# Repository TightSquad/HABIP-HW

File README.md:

# The Custom PCB Hardware repo for the HABIP
Main code repo for the HABIP: [HABIP](https://github.com/TightSquad/HABIP "HABIP Repo")

MSP430 firmware repo for the HABIP: [HABIP-MSP430](https://github.com/TightSquad/HABIP-MSP430 "HABIP-MSP430 Repo")

Communication Systems Team Website: [COMMS](http://edge.rit.edu/edge/P17104/public/Home "COMM's Website")

Data Acquisition & Control Systems Team Website: [DAQCS](http://edge.rit.edu/edge/P17105/public/Home "DAQCS's Website")

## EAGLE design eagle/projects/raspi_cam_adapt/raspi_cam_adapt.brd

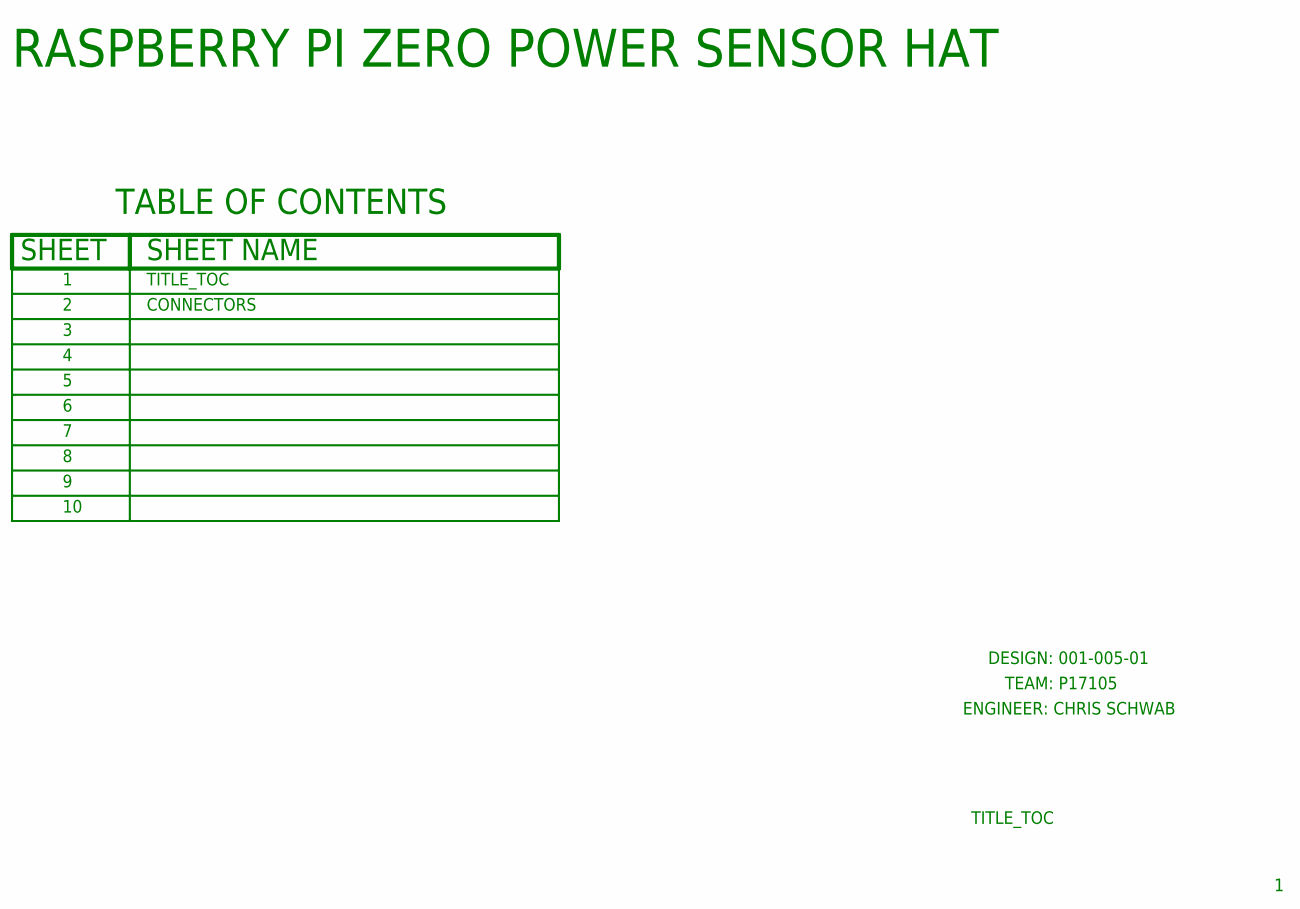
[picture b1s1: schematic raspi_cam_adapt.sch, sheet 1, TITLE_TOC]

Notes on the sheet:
RASPBERRY PI ZERO POWER SENSOR HAT
TITLE_TOC
CONNECTORS
ENGINEER: CHRIS SCHWAB
TEAM: P17105
DESIGN: 001-005-01

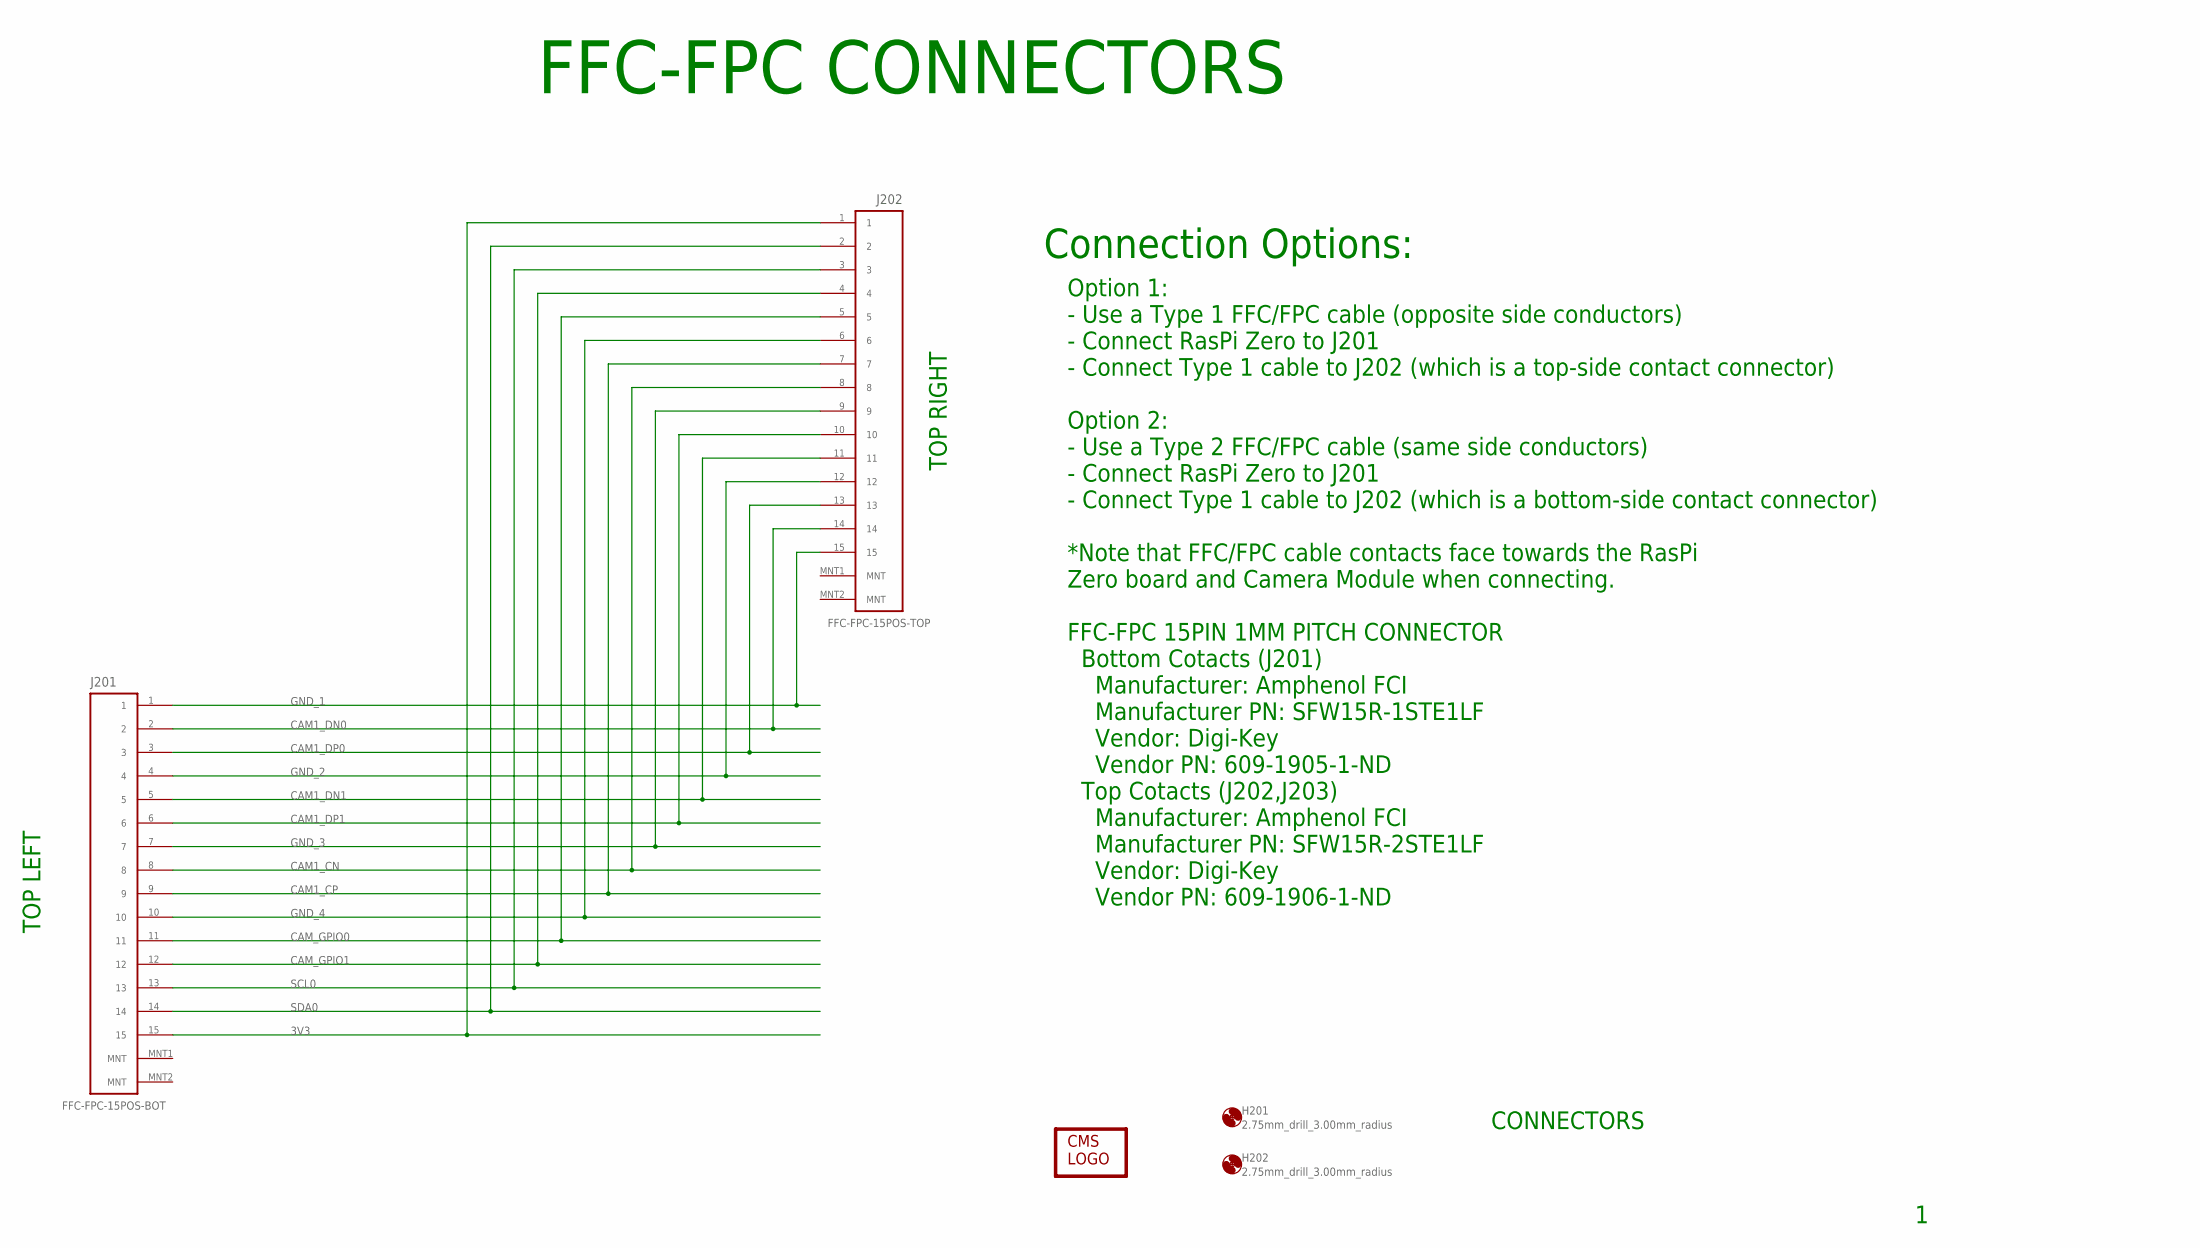
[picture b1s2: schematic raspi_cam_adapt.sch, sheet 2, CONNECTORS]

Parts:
H201, H202: 2.75mm_drill_3.00mm_radius; 2,75_3,0_HOLE_RASPI
J201: FFC-FPC-15POS-BOT; FFC-FPC-100P060X200-15N
J202: FFC-FPC-15POS-TOP; FFC-FPC-100P060X200-15N
LOGO201: CMS_LOGO

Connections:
3V3: J201.15, J202.1
CAM1_CN: J201.8, J202.8
CAM1_CP: J201.9, J202.7
CAM1_DN0: J201.2, J202.14
CAM1_DN1: J201.5, J202.11
CAM1_DP0: J201.3, J202.13
CAM1_DP1: J201.6, J202.10
CAM_GPIO0: J201.11, J202.5
CAM_GPIO1: J201.12, J202.4
GND_1: J201.1, J202.15
GND_2: J201.4, J202.12
GND_3: J201.7, J202.9
GND_4: J201.10, J202.6
SCL0: J201.13, J202.3
SDA0: J201.14, J202.2

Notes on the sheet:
FFC-FPC CONNECTORS
TOP LEFT
TOP RIGHT
Connection Options:
Option 1: - Use a Type 1 FFC/FPC cable (opposite side conductors) - Connect RasPi Zero to J201 - Connect Type 1 cable to J202 (which is a top-side contact connector) Option 2: - Use a Type 2 FFC/FPC cable (same side conductors) - Connect RasPi Zero to J201 - Connect Type 1 cable to J202 (which is a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
CONNECTORS

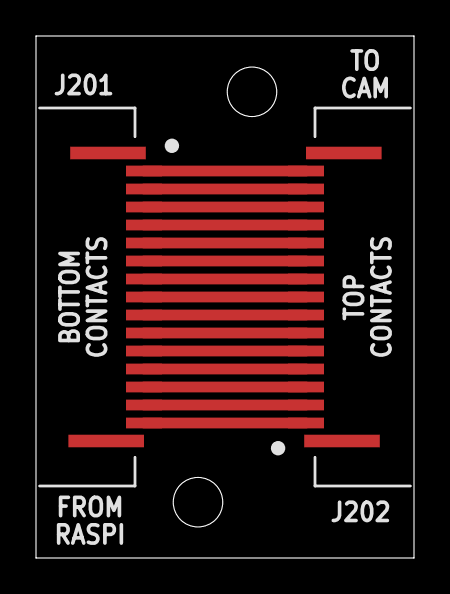
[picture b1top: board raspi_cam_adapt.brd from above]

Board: 4 copper layers, 21.0 x 29.0 mm, 5 parts (1 on the bottom side), 15 nets.

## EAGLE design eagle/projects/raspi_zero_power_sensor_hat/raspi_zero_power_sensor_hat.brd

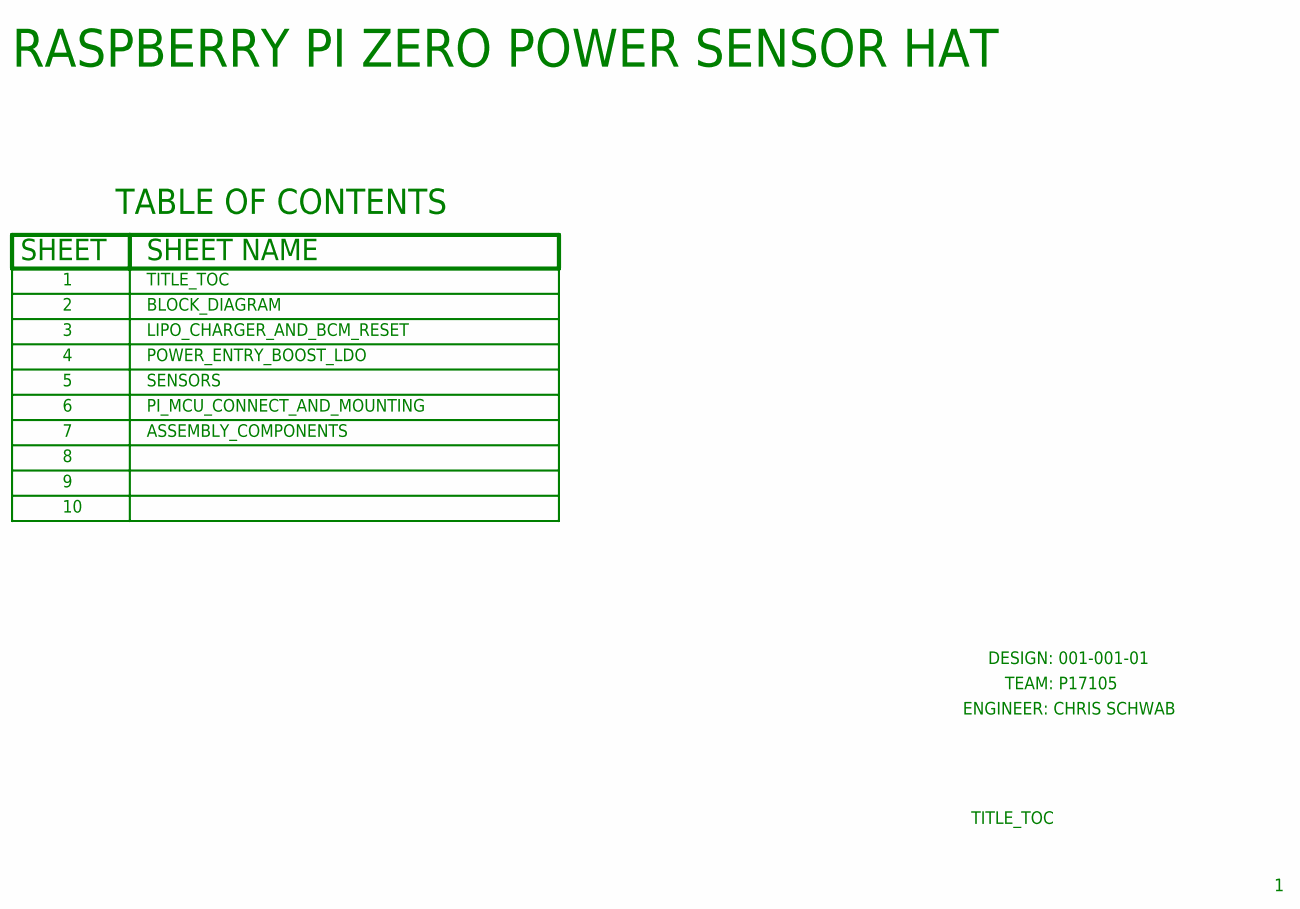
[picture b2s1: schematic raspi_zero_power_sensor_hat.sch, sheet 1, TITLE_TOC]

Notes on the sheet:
RASPBERRY PI ZERO POWER SENSOR HAT
TITLE_TOC
BLOCK_DIAGRAM
ENGINEER: CHRIS SCHWAB
TEAM: P17105
LIPO_CHARGER_AND_BCM_RESET
SENSORS
PI_MCU_CONNECT_AND_MOUNTING
POWER_ENTRY_BOOST_LDO
ASSEMBLY_COMPONENTS
DESIGN: 001-001-01

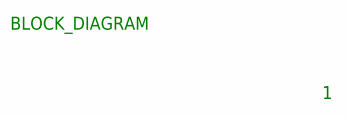
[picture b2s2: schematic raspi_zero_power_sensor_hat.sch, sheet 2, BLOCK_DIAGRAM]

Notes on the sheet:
BLOCK_DIAGRAM

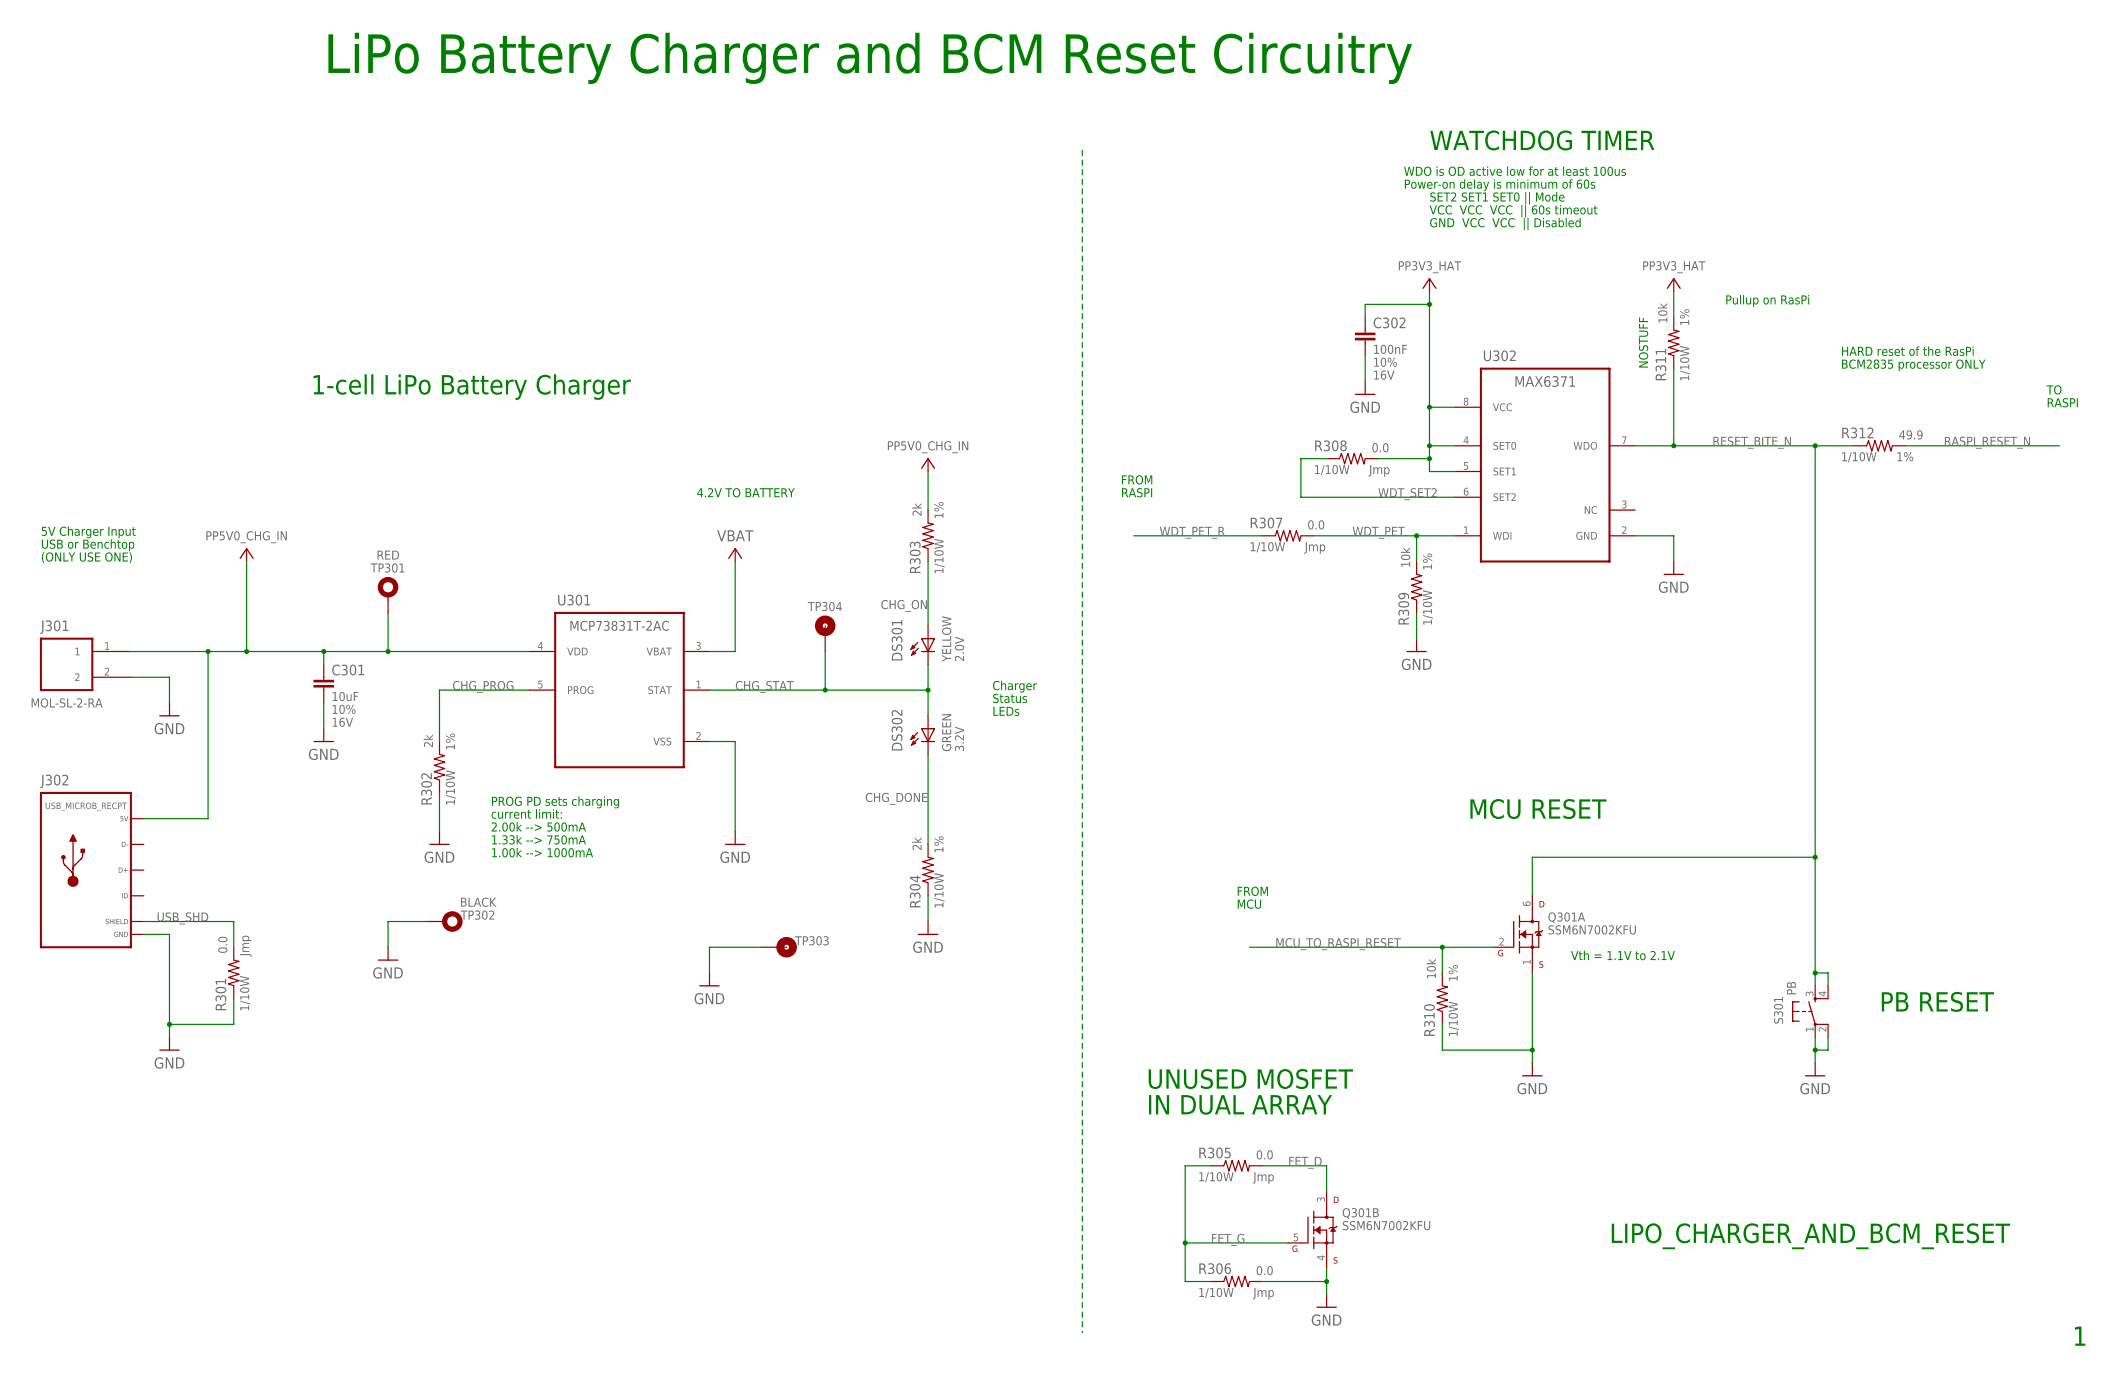
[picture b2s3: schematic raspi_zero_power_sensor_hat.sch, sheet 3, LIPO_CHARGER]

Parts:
C301: 10uF; C0805
C302: 100nF; C0603
DS301: YELLOW; LED0603
DS302: GREEN; LED0603
J301: MOL-SL-2-RA; MOLSL-2-RA_HALF
J302: USB_MICROB_RECPT; MICROUSB-RIGHT
Q301: SSM6N7002KFU; SOT363P080X040-6N
R301, R305, R306, R307, R308: 0.0; R0603
R302, R303, R304: 2k; R0603
R309, R310, R311: 10k; R0603
R312: 49.9; R0603
S301: PB; TACTILE-PTH
TP301: TEST_POINT_TH_D102_R; TP_TH102
TP302: TEST_POINT_TH_D102_B; TP_TH102
TP303: TEST_POINT_SMT_20R_SMD; TP20R
TP304: TEST_POINT_SMT_15R_SMD; TP15R
U301: MCP73831T-2AC; SOT23P110X060-5N
U302: MAX6371; SOT23P130X045-8N

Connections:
CHG_DONE: DS302.1 (C), R304.2
CHG_ON: DS301.2 (A), R303.1
CHG_PROG: R302.2, U301.5 (PROG)
CHG_STAT: DS301.1 (C), DS302.2 (A), TP304.TP, U301.1 (STAT)
FET_D: Q301.3 (D), R305.2
FET_G: Q301.5 (G), R305.1, R306.1
GND: C301.2, C302.2, J301.2, J302.5 (GND), Q301.1 (S), Q301.4 (S), R301.1, R302.1, R304.1, R306.2, R309.1, R310.1, S301.1, S301.2, TP302.1, TP303.TP, U301.2 (VSS), U302.2 (GND); also elsewhere on the board
MCU_TO_RASPI_RESET: Q301.2 (G), R310.2; also elsewhere on the board
PP3V3_HAT: C302.1, R308.2, R311.2, U302.4 (SET0), U302.5 (SET1), U302.8 (VCC); also elsewhere on the board
PP5V0_CHG_IN: C301.1, J301.1, J302.1 (5V), R303.2, TP301.1, U301.4 (VDD); also elsewhere on the board
RASPI_RESET_N: R312.2; also elsewhere on the board
RESET_BITE_N: Q301.6 (D), R311.1, R312.1, S301.3, S301.4, U302.7 (WDO)
USB_SHD: J302.S1 (SLD), J302.S2 (SLD), J302.S3 (SLD), J302.S4 (SLD), J302.S5 (SLD), J302.S6 (SLD), R301.2
VBAT: U301.3 (VBAT); also elsewhere on the board
WDT_PET: R307.2, R309.2, U302.1 (WDI)
WDT_PET_R: R307.1; also elsewhere on the board
WDT_SET2: R308.1, U302.6 (SET2)

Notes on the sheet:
LIPO_CHARGER_AND_BCM_RESET
PROG PD sets charging
current limit:
Charger
Status
LEDs
LiPo Battery Charger and BCM Reset Circuitry
1.00k --> 1000mA
1.33k --> 750mA
2.00k --> 500mA
5V Charger Input
USB or Benchtop
4.2V TO BATTERY
WATCHDOG TIMER
WDO is OD active low for at least 100us
Power-on delay is minimum of 60s
SET2 SET1 SET0 || Mode
VCC VCC VCC || 60s timeout
GND VCC VCC || Disabled
FROM
RASPI
1-cell LiPo Battery Charger
NOSTUFF
MCU
HARD reset of the RasPi
PB RESET
BCM2835 processor ONLY
(ONLY USE ONE)
Vth = 1.1V to 2.1V
MCU RESET
UNUSED MOSFET
IN DUAL ARRAY
Pullup on RasPi

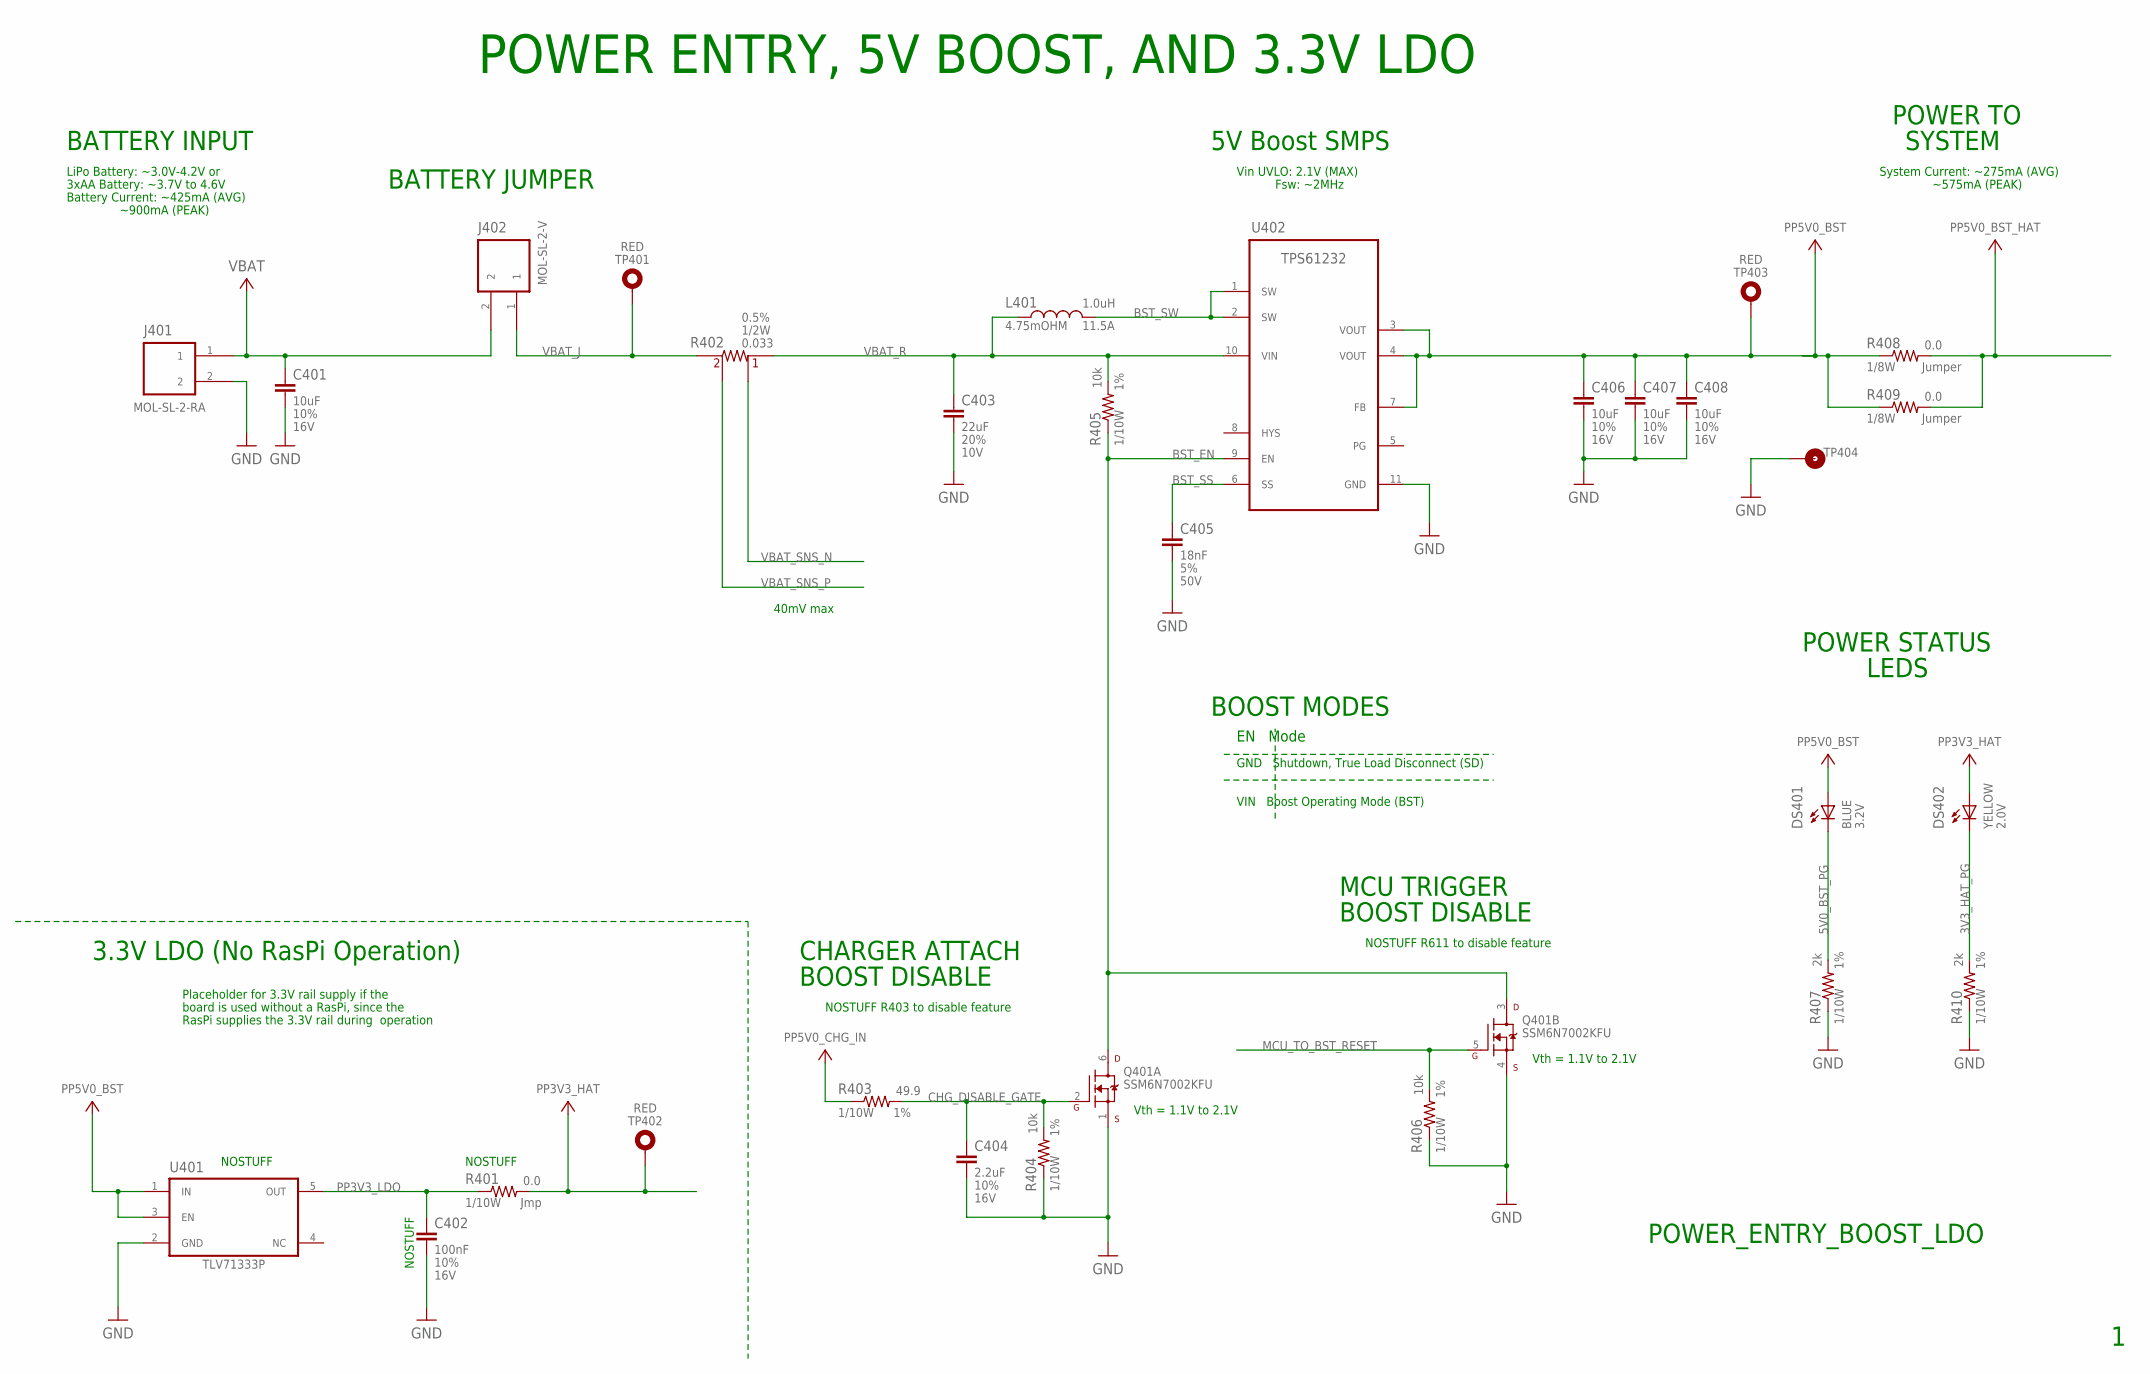
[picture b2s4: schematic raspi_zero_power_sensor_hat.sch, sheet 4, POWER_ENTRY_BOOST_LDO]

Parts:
C401, C406, C407, C408: 10uF; C0805
C402: 100nF; C0603
C403: 22uF; C0805
C404: 2.2uF; C0603
C405: 18nF; C0603
DS401: BLUE; LED0603
DS402: YELLOW; LED0603
J401: MOL-SL-2-RA; MOLSL-2-RA
J402: MOL-SL-2-V; MOLSL-2-V
L401: 1.0uH; SMD410P190X160-2N
Q401: SSM6N7002KFU; SOT363P080X040-6N
R401: 0.0; R0603
R402: 0.033; RS1206
R403: 49.9; R0603
R404, R405, R406: 10k; R0603
R407, R410: 2k; R0603
R408, R409: 0.0; R0805
TP401, TP402, TP403: TEST_POINT_TH_D102_R; TP_TH102
TP404: TEST_POINT_SMT_15R_SMD; TP15R
U401: TLV71333P; SOT23P105X060-5N
U402: TPS61232; DRC0010G_SM

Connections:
3V3_HAT_PG: DS402.1 (C), R410.2
5V0_BST_PG: DS401.1 (C), R407.2
BST_EN: Q401.3 (D), Q401.6 (D), R405.1, U402.9 (EN)
BST_SS: C405.1, U402.6 (SS)
BST_SW: L401.2, U402.1 (SW), U402.2 (SW)
CHG_DISABLE_GATE: C404.1, Q401.2 (G), R403.2, R404.2
GND: C401.2, C402.2, C403.2, C404.2, C405.2, C406.2, C407.2, C408.2, J401.2, Q401.1 (S), Q401.4 (S), R404.1, R406.1, R407.1, R410.1, TP404.TP, U401.2 (GND), U402.11 (GND); also elsewhere on the board
MCU_TO_BST_RESET: Q401.5 (G), R406.2; also elsewhere on the board
PP3V3_HAT: DS402.2 (A), R401.2, TP402.1; also elsewhere on the board
PP3V3_LDO: C402.1, R401.1, U401.5 (OUT)
PP5V0_BST: C406.1, C407.1, C408.1, DS401.2 (A), R408.1, R409.1, TP403.1, U401.1 (IN), U401.3 (EN), U402.3 (VOUT), U402.4 (VOUT), U402.7 (FB)
PP5V0_BST_HAT: R408.2, R409.2; also elsewhere on the board
PP5V0_CHG_IN: R403.1; also elsewhere on the board
VBAT: C401.1, J401.1, J402.2; also elsewhere on the board
VBAT_J: J402.1, R402.2A, TP401.1
VBAT_R: C403.1, L401.1, R402.1A, R405.2, U402.10 (VIN)
VBAT_SNS_N: R402.1V; also elsewhere on the board
VBAT_SNS_P: R402.2V; also elsewhere on the board

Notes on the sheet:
POWER ENTRY, 5V BOOST, AND 3.3V LDO
5V Boost SMPS
LiPo Battery: ~3.0V-4.2V or
3xAA Battery: ~3.7V to 4.6V
Battery Current: ~425mA (AVG)
~900mA (PEAK)
System Current: ~275mA (AVG)
~575mA (PEAK)
POWER TO
SYSTEM
POWER STATUS
LEDS
POWER_ENTRY_BOOST_LDO
Vin UVLO: 2.1V (MAX)
3.3V LDO (No RasPi Operation)
Placeholder for 3.3V rail supply if the
board is used without a RasPi, since the
RasPi supplies the 3.3V rail during operation
NOSTUFF
BATTERY INPUT
BOOST MODES
EN Mode
GND Shutdown, True Load Disconnect (SD)
VIN Boost Operating Mode (BST)
CHARGER ATTACH
BOOST DISABLE
MCU TRIGGER
NOSTUFF R403 to disable feature
NOSTUFF R611 to disable feature
Vth = 1.1V to 2.1V
Fsw: ~2MHz
BATTERY JUMPER
40mV max

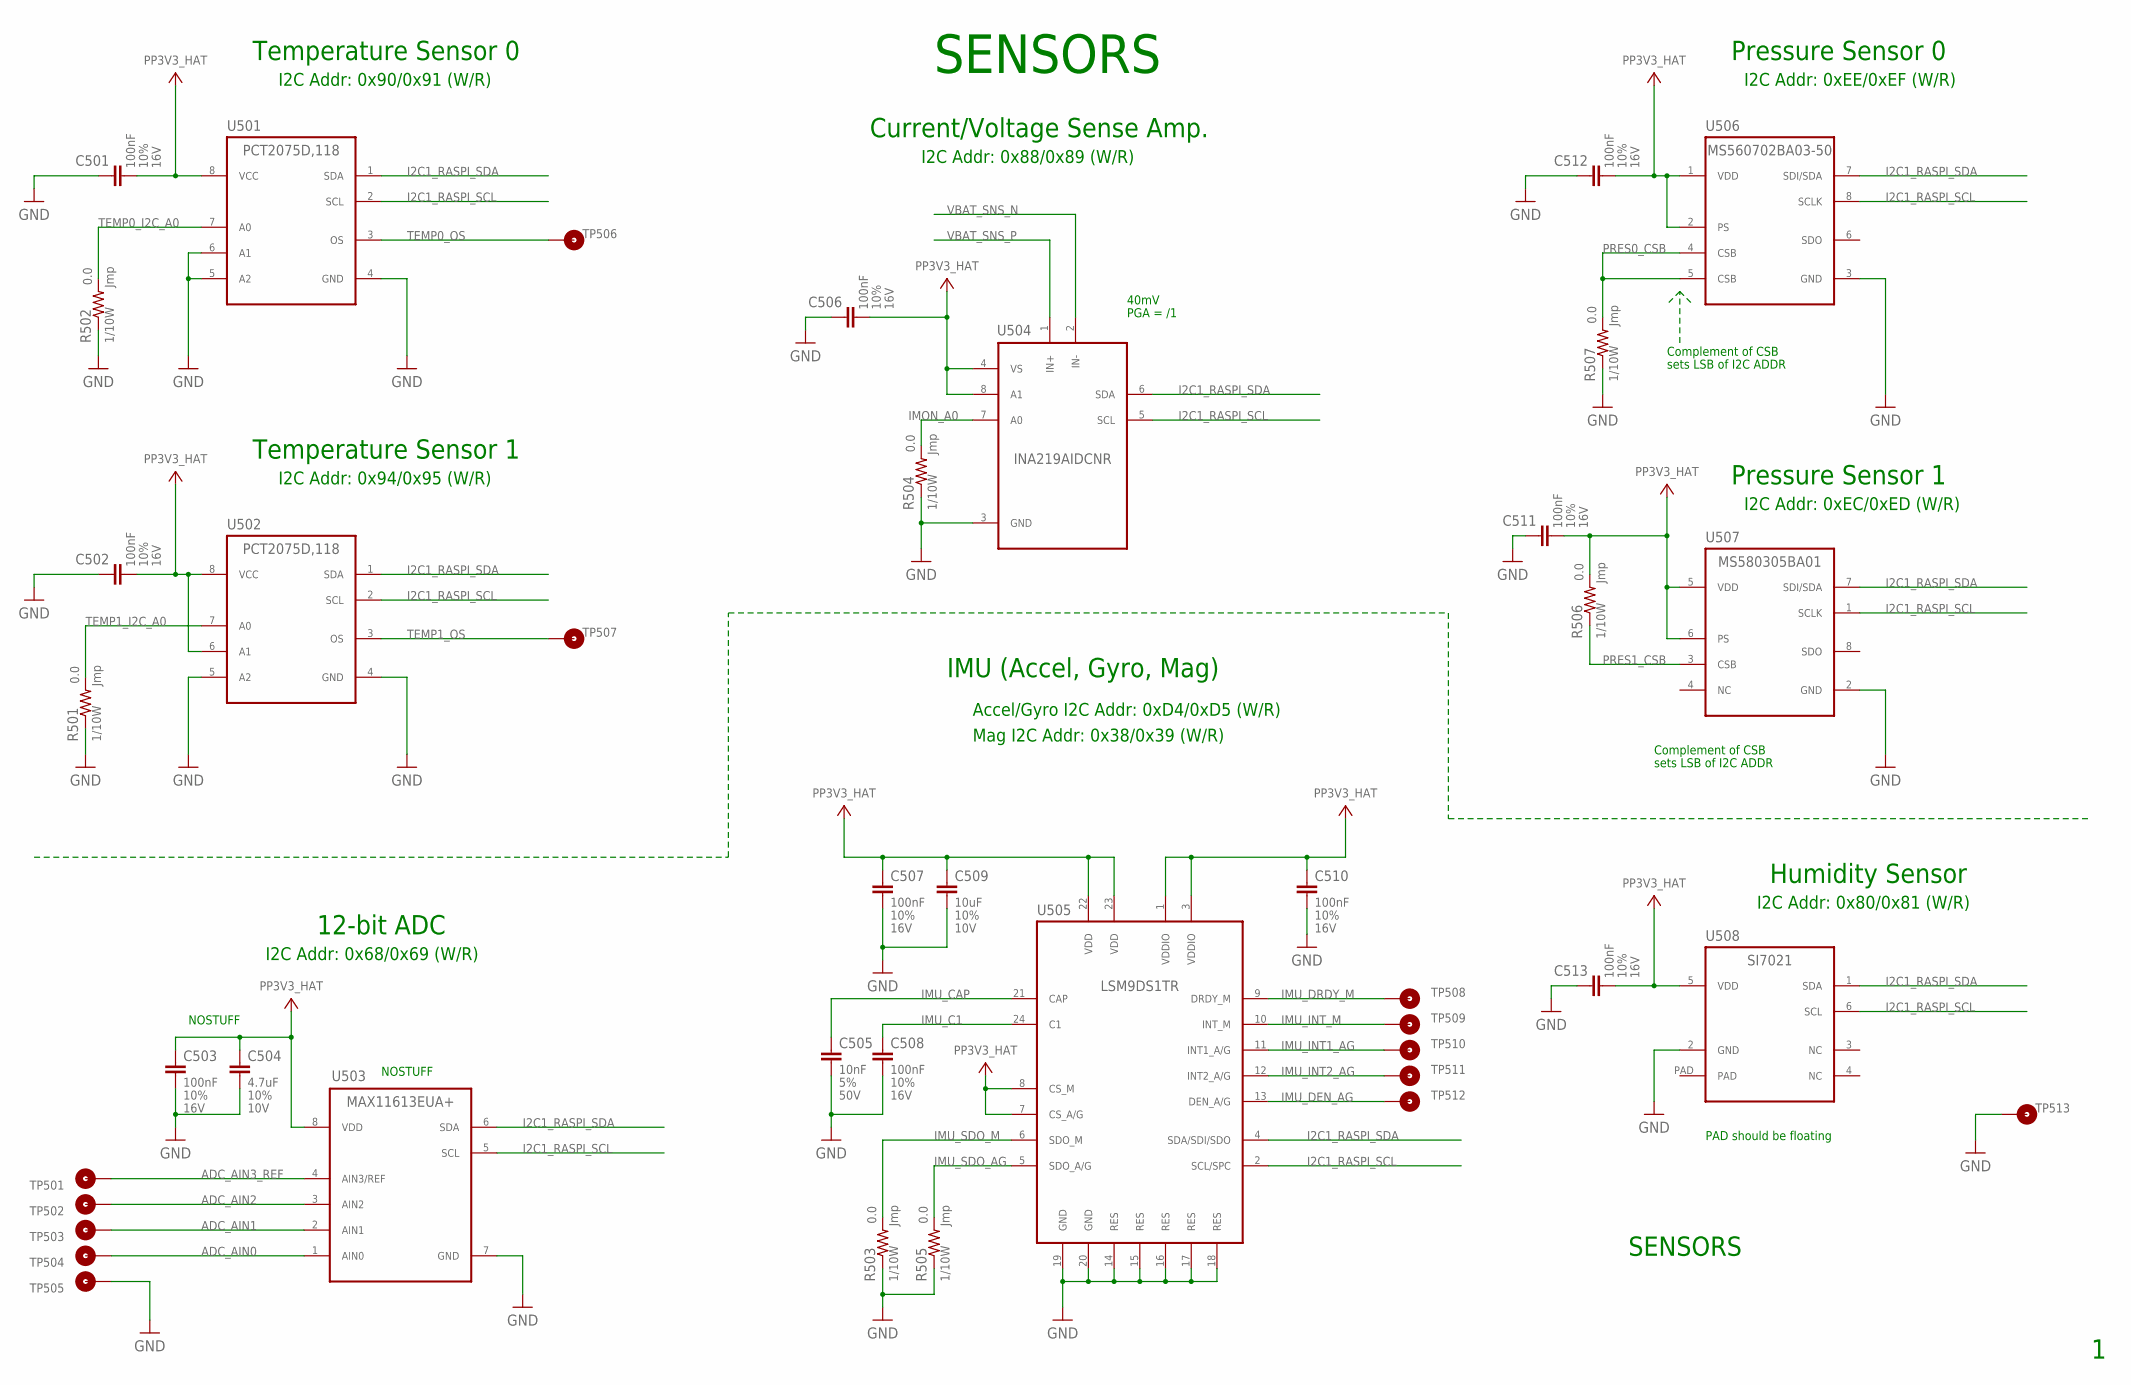
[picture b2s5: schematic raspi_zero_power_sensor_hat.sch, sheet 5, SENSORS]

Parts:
C501, C502, C503, C506, C507, C508, C510, C511, C512, C513: 100nF; C0603
C504: 4.7uF; C0603
C505: 10nF; C0603
C509: 10uF; C0603
R501, R502, R503, R504, R505, R506, R507: 0.0; R0603
TP501, TP502, TP503, TP504, TP505, TP513: TEST_POINT_SMT_20R_SMD; TP20R
TP506, TP507, TP508, TP509, TP510, TP511, TP512: TEST_POINT_SMT_15R_SMD; TP15R
U501, U502: PCT2075D,118; SOIC127P130X0600-8N
U503: MAX11613EUA+; SOP65P135X040-8N
U504: INA219AIDCNR; SOT65P110X045-8N
U505: LSM9DS1TR; LGA043P045X033-24N
U506: MS560702BA03-50; SMD125P110X060-8N
U507: MS580305BA01; SMD125130P225X090-8N
U508: SI7021; DFN-100P085X045-T-6N

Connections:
ADC_AIN0: TP504.TP, U503.1 (AIN0)
ADC_AIN1: TP503.TP, U503.2 (AIN1)
ADC_AIN2: TP502.TP, U503.3 (AIN2)
ADC_AIN3_REF: TP501.TP, U503.4 (AIN3/REF)
GND: C501.1, C502.1, C503.2, C504.2, C505.2, C506.1, C507.2, C508.2, C509.2, C510.2, C511.1, C512.1, C513.1, R501.1, R502.1, R503.1, R504.1, R505.1, R507.1, TP505.TP, TP513.TP, U501.4 (GND), U501.5 (A2), U501.6 (A1), U502.4 (GND), U502.5 (A2), U503.7 (GND), U504.3 (GND), U505.14 (RES), U505.15 (RES), U505.16 (RES), U505.17 (RES), U505.18 (RES), U505.19 (GND), U505.20 (GND), U506.3 (GND), U507.2 (GND), U508.2 (GND); also elsewhere on the board
I2C1_RASPI_SCL: U501.2 (SCL), U502.2 (SCL), U503.5 (SCL), U504.5 (SCL), U505.2 (SCL/SPC), U506.8 (SCLK), U507.1 (SCLK), U508.6 (SCL); also elsewhere on the board
I2C1_RASPI_SDA: U501.1 (SDA), U502.1 (SDA), U503.6 (SDA), U504.6 (SDA), U505.4 (SDA/SDI/SDO), U506.7 (SDI/SDA), U507.7 (SDI/SDA), U508.1 (SDA); also elsewhere on the board
IMON_A0: R504.2, U504.7 (A0)
IMU_C1: C508.1, U505.24 (C1)
IMU_CAP: C505.1, U505.21 (CAP)
IMU_DEN_AG: TP512.TP, U505.13 (DEN_A/G)
IMU_DRDY_M: TP508.TP, U505.9 (DRDY_M)
IMU_INT1_AG: TP510.TP, U505.11 (INT1_A/G)
IMU_INT2_AG: TP511.TP, U505.12 (INT2_A/G)
IMU_INT_M: TP509.TP, U505.10 (INT_M)
IMU_SDO_AG: R505.2, U505.5 (SDO_A/G)
IMU_SDO_M: R503.2, U505.6 (SDO_M)
PP3V3_HAT: C501.2, C502.2, C503.1, C504.1, C506.2, C507.1, C509.1, C510.1, C511.2, C512.2, C513.2, R506.2, U501.8 (VCC), U502.6 (A1), U502.8 (VCC), U503.8 (VDD), U504.4 (VS), U504.8 (A1), U505.1 (VDDIO), U505.3 (VDDIO), U505.7 (CS_A/G), U505.8 (CS_M), U505.22 (VDD), U505.23 (VDD), U506.1 (VDD), U506.2 (PS), U507.5 (VDD), U507.6 (PS), U508.5 (VDD); also elsewhere on the board
PRES0_CSB: R507.2, U506.4 (CSB), U506.5 (CSB)
PRES1_CSB: R506.1, U507.3 (CSB)
TEMP0_I2C_A0: R502.2, U501.7 (A0)
TEMP0_OS: TP506.TP, U501.3 (OS)
TEMP1_I2C_A0: R501.2, U502.7 (A0)
TEMP1_OS: TP507.TP, U502.3 (OS)
VBAT_SNS_N: U504.2 (IN-); also elsewhere on the board
VBAT_SNS_P: U504.1 (IN+); also elsewhere on the board

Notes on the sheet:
SENSORS
12-bit ADC
Current/Voltage Sense Amp.
Temperature Sensor 0
Pressure Sensor 0
I2C Addr: 0x68/0x69 (W/R)
I2C Addr: 0x88/0x89 (W/R)
I2C Addr: 0x90/0x91 (W/R)
Complement of CSB
sets LSB of I2C ADDR
I2C Addr: 0xEE/0xEF (W/R)
Temperature Sensor 1
I2C Addr: 0x94/0x95 (W/R)
Pressure Sensor 1
I2C Addr: 0xEC/0xED (W/R)
Humidity Sensor
NOSTUFF
I2C Addr: 0x80/0x81 (W/R)
IMU (Accel, Gyro, Mag)
Accel/Gyro I2C Addr: 0xD4/0xD5 (W/R)
Mag I2C Addr: 0x38/0x39 (W/R)
PGA = /1
40mV
PAD should be floating

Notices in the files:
parts and their libraries:
grss: Copyright (C) 2015 Accelerated Designs. All rights reserved
